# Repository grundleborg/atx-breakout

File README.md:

atx-breakout
============

PCB Layout for an ATX Power Supply to Molex Connector Breakout Board.

Made in eagle 6.5.0 for Linux.

This board has a socket for one ATX 20 pin power connector, and breaks out every line on that socket
to a molex header. Each voltage goes to a two pin voltage and ground molex header, and the remaining
bits go to a 4 pin one.

Take a look at the board and schematic - it's pretty simple really.

The traces are 50mil wide - anecdotally that's enough for quite a high current, but if you are
worried about that, you should check yourself and modify it before getting the boards etched.

The board is designed to be within the 5cm x 10cm 2-Layer PCB constraints offered at
http://imall.iteadstudio.com/open-pcb/pcb-prototyping.html

Unfortunately, the 5cm x 5cm board is too small for the ATX connector.

Release branches/tags contain a folder called gerber with the files prepared by the imall CAM
processor ready to send directly to them to get it etched. However, please make sure you check
before sending them (e.g. using an online gerber viewer), as I don't accept any responsibility for
your PCBs coming back wrong even if you use files from here unmodified!

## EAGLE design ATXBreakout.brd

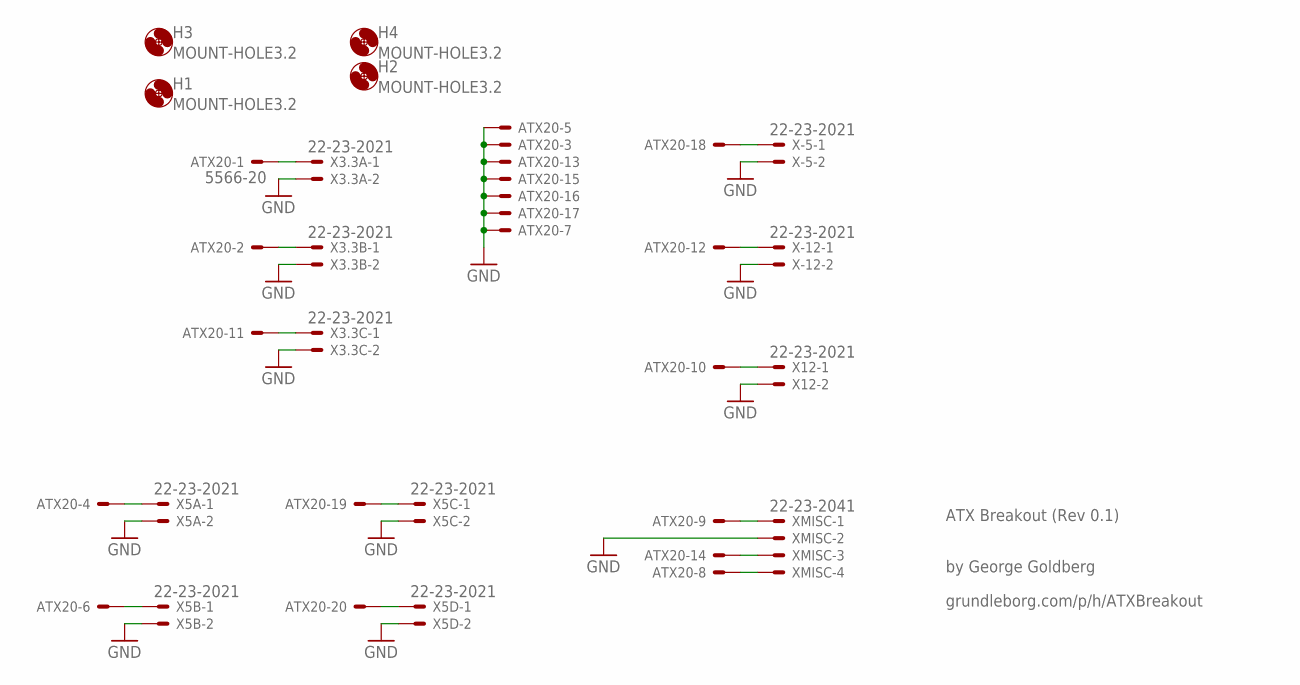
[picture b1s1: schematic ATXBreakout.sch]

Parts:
ATX20: 5566-20
H1, H2, H3, H4: MOUNT-HOLE3.2; 3,2
X3.3A, X3.3B, X3.3C, X5A, X5B, X5C, X5D, X12: 22-23-2021
X-5, X-12: 22-23-2021
XMISC: 22-23-2041

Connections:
GND: ATX20.3, ATX20.5, ATX20.7, ATX20.13, ATX20.15, ATX20.16, ATX20.17, X3.3A.2, X3.3B.2, X3.3C.2, X5A.2, X5B.2, X5C.2, X5D.2, X12.2, X-5.2, X-12.2, XMISC.2
unnamed: ATX20.1, X3.3A.1
unnamed: ATX20.2, X3.3B.1
unnamed: ATX20.11, X3.3C.1
unnamed: ATX20.4, X5A.1
unnamed: ATX20.6, X5B.1
unnamed: ATX20.19, X5C.1
unnamed: ATX20.20, X5D.1
unnamed: ATX20.18, X-5.1
unnamed: ATX20.12, X-12.1
unnamed: ATX20.9, XMISC.1
unnamed: ATX20.14, XMISC.3
unnamed: ATX20.8, XMISC.4
unnamed: ATX20.10, X12.1

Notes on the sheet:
ATX Breakout (Rev 0.1)
by George Goldberg
grundleborg.com/p/h/ATXBreakout

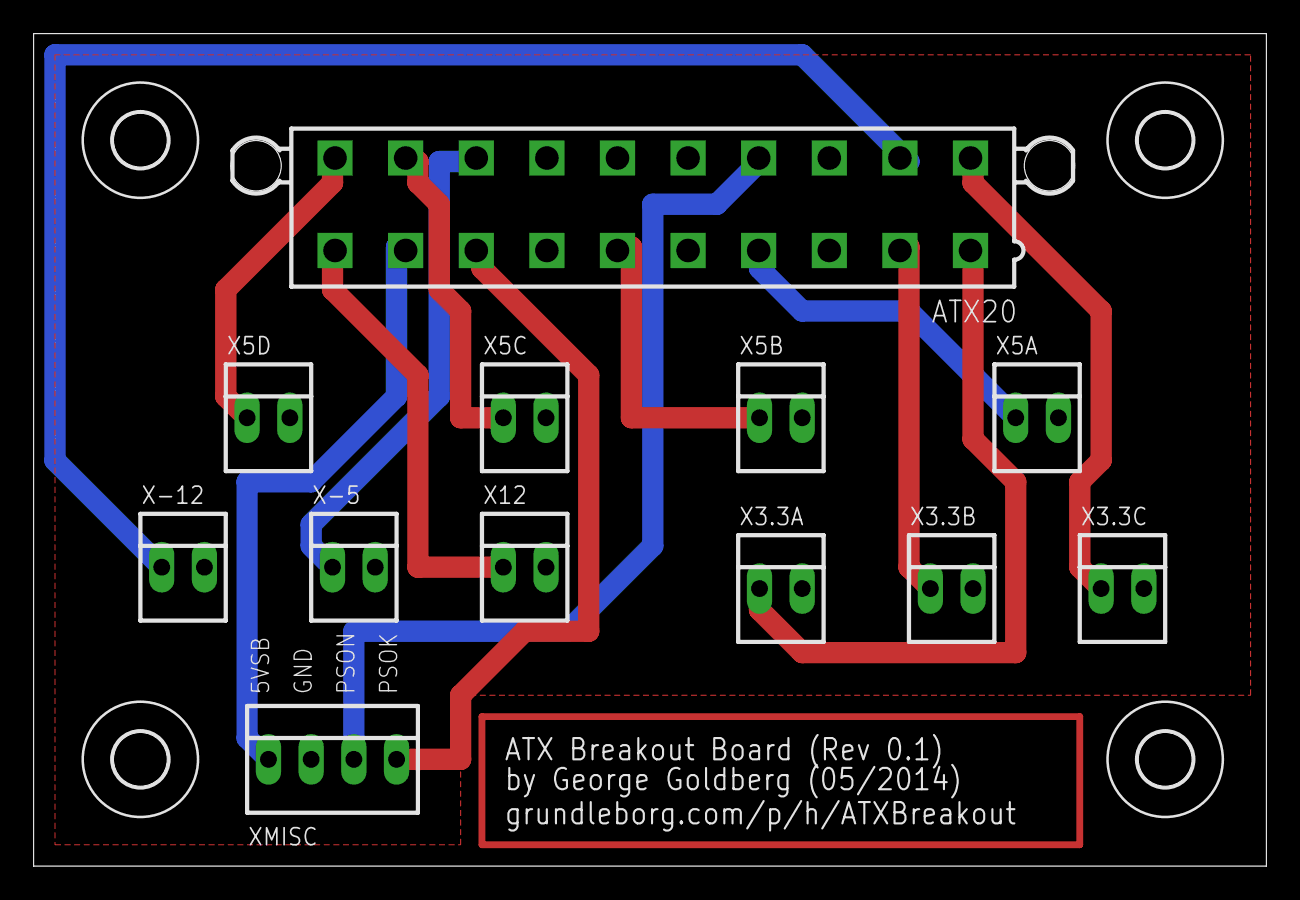
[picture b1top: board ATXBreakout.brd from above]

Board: 2 copper layers, 73.3 x 49.5 mm, 16 parts (0 on the bottom side), 14 nets.

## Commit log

2014-05-25 Commit board and schematic of first version.
2014-05-25 Flesh out README.
2014-05-25 Generate the iMall gerber files.
